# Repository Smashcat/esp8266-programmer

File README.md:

# esp8266-programmer
Eagle files for a small ESP8266 programmer with auto-programming mode/reset

This uses mostly SMD parts, so really needs to be cooked in an oven or hotplate due to the density (difficult to get an iron into the right places). I've also included the library part for the USB port, as I found the version online (at Octopart) has an incorrect footprint. I ordered 10 of these, plus a stencil from JLCPCB at a cost of $8, plus shipping! I would suggest getting the stencil if you intend to make a few, as it saves a ton of time, and makes the board look a lot cleaner.

The board can supply around 400mA of current at 3.3v, so should easily be able to power an ESP8266 module, with plenty to spare for other components such as an LCD etc if needed. If you're already powering the ESP from another source, then do not connect the 3v3 pin from the programmer.

There are LEDs on each of the active pins, plus 3v3, so you can see activity at all times. It also means that it's possible to control the LEDs on the programmer via the GPIO0, RX and TX pins on the ESP if you like (pull them low to light the LED). The LEDs and their resistors are optional - the programmer will still work without them.

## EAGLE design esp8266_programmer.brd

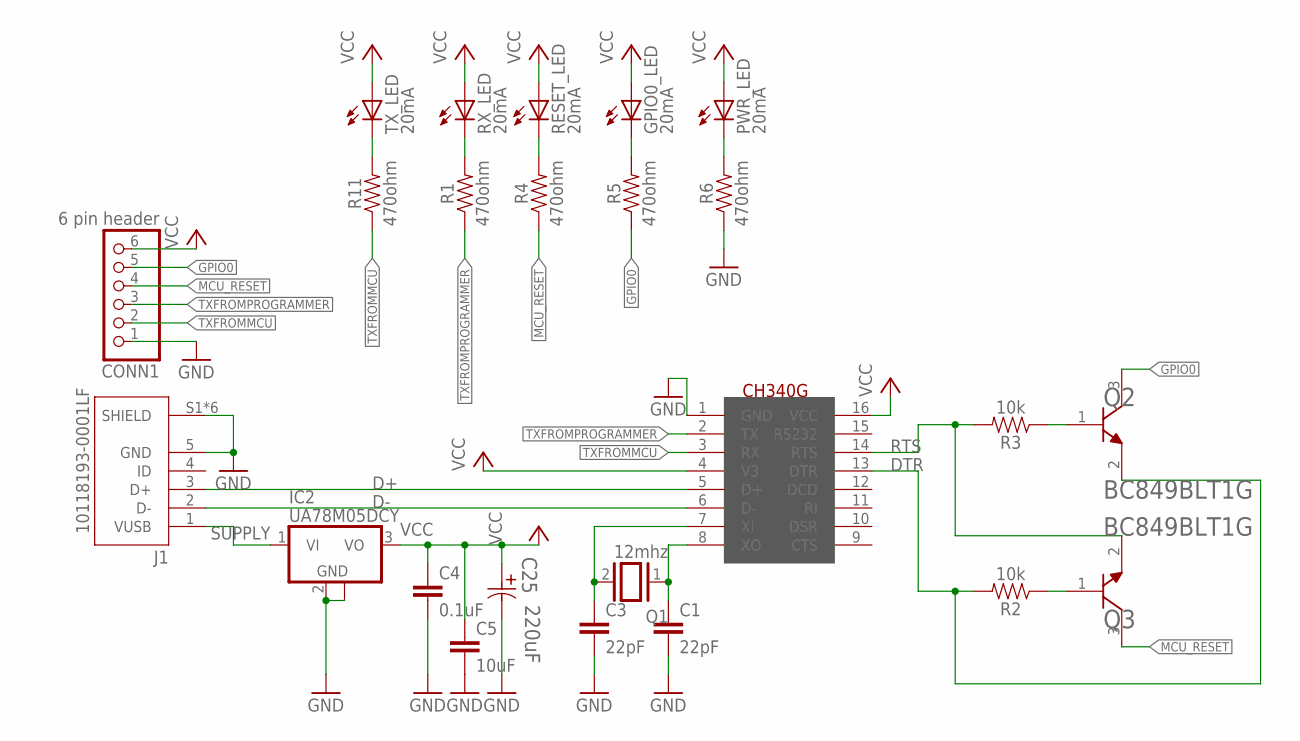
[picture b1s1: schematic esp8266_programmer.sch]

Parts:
C1, C3: 22pF; C0603
C4: 0.1uF; C0603
C5: 10uF; C0603
C25: 220uF; CAPAE830X1050N
CONN1: 6 pin header; 1X06
GPIO0_LED: 20mA; CHIP-LED0603
IC2: UA78M05DCY; SOT223
J1: 10118193-0001LF; FCI_10118193-0001LF
PWR_LED: 20mA; CHIP-LED0603
Q1: 12mhz; QS
Q2, Q3: ON_SEMICONDUCTOR_BC849BLT1GON_SEMICONDUCTOR_BC849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; ON_SEMICONDUCTOR_BC849BLT1G_0
R1, R4, R5, R6, R11: 470ohm; 0603
R2, R3: 10k; 0603
RESET_LED: 20mA; CHIP-LED0603
RX_LED: 20mA; CHIP-LED0603
TX_LED: 20mA; CHIP-LED0603
U$1: CH340G; SOIC16

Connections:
CRYSTALIN: C3.1, Q1.2, U$1.7 (XI)
CRYSTALOUT: C1.1, Q1.1, U$1.8 (XO)
D+: J1.3 (D+), U$1.5 (D+)
D-: J1.2 (D-), U$1.6 (D-)
DTR: Q2.2 (E), R2.2, U$1.13 (DTR)
GND: C1.2, C3.2, C4.2, C5.2, C25.2, CONN1.1, IC2.2 (GND), IC2.4 (GND), J1.5 (GND), J1.S1 (SHIELD), J1.S2 (SHIELD), J1.S3 (SHIELD), J1.S4 (SHIELD), J1.S5 (SHIELD), J1.S6 (SHIELD), R6.1, U$1.1 (GND)
GPIO0: CONN1.5, Q2.3 (C), R5.1
MCU_RESET: CONN1.4, Q3.3 (C), R4.1
unnamed: Q3.1 (B), R2.1
unnamed: Q2.1 (B), R3.1
RTS: Q3.2 (E), R3.2, U$1.14 (RTS)
STATUSTOLED: R11.2, TX_LED.C
STATUSTOLED1: R1.2, RX_LED.C
STATUSTOLED2: R4.2, RESET_LED.C
STATUSTOLED3: GPIO0_LED.C, R5.2
STATUSTOLED4: PWR_LED.C, R6.2
SUPPLY: IC2.1 (VI), J1.1 (VUSB)
TXFROMMCU: CONN1.2, R11.1, U$1.3 (RX)
TXFROMPROGRAMMER: CONN1.3, R1.1, U$1.2 (TX)
VCC: C4.1, C5.1, C25.1, CONN1.6, GPIO0_LED.A, IC2.3 (VO), PWR_LED.A, RESET_LED.A, RX_LED.A, TX_LED.A, U$1.4 (V3), U$1.16 (VCC)

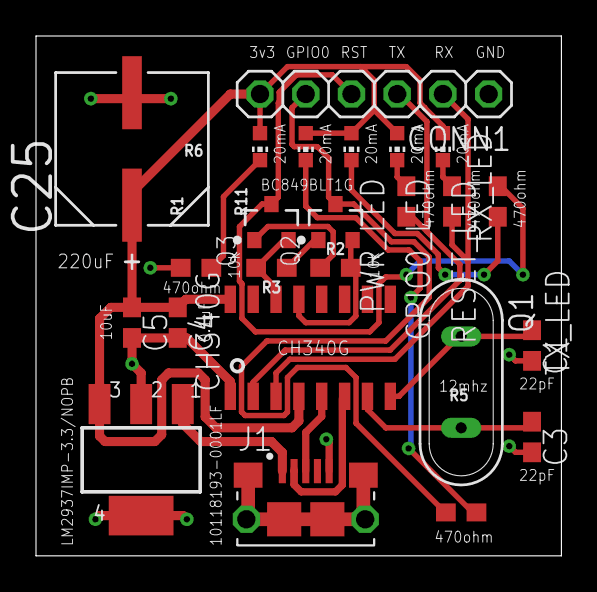
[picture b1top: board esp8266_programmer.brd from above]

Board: 2 copper layers, 29.2 x 28.9 mm, 24 parts (0 on the bottom side), 20 nets.

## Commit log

2018-12-29 Adde schematics
2018-12-29 Added library for USB port
2018-12-29 Added gerber zip for JLCPCB
2018-12-30 Create LICENSE
2019-01-02 Update issue templates

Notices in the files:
parts and their libraries:
SparkFun-Resistors: Licensing: Creative Commons ShareAlike 4.0 International - https://creativecommons.org/licenses/by-sa/4.0
